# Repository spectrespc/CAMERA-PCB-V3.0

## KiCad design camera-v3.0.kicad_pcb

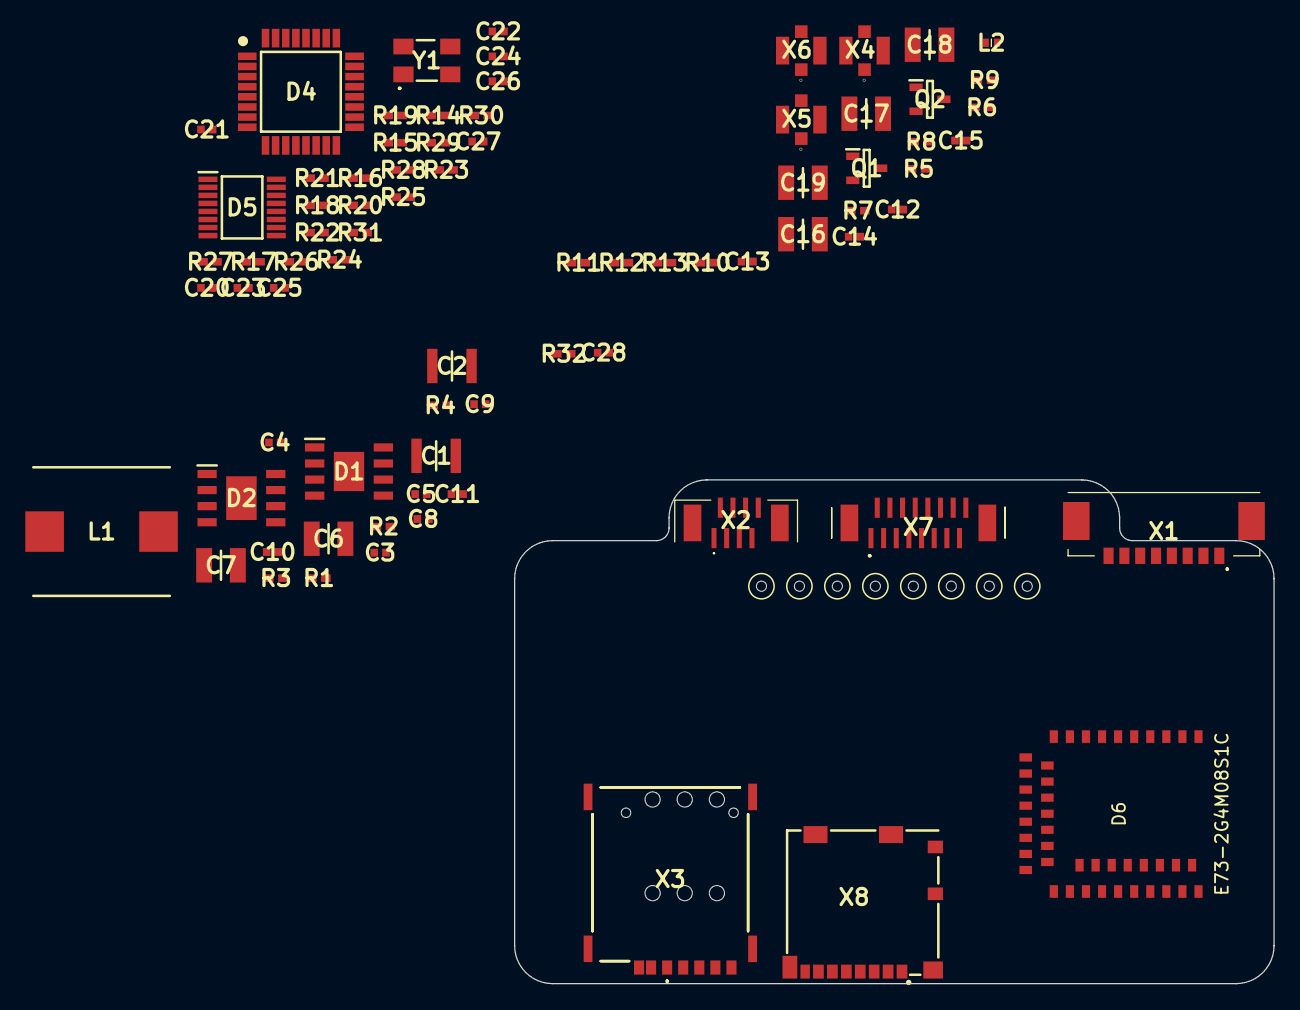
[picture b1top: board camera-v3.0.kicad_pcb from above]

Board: 2 copper layers, 60.0 x 39.8 mm, 79 parts (1 on the bottom side), 58 nets, no tracks yet.

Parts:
C1, C2: 10u; CAPC3225X150N
C3, C8: 150p; CAPC1005X55N
C4, C11: 15n; CAPC1005X55N
C5, C15: 0.1u; CAPC1005X55N
C6, C7, C16, C17, C18, C19: 22u; CAPC3225X270N
C9, C10, C20, C21, C22, C25, C26, C27, C28: 1u; CAPC1005X55N
C12, C13, C14, C23, C24: 16p; CAPC1005X55N
D1: TPS54334DDA; SOIC127P600X170-9N
D2: ADP1706ARDZ-3.3-R7; SOIC127P600X175-9N
D3: SIM7600E-H; IC_SIM7600E-H
D4: TUSB2046BVF; QFP80P900X900X160-32N
D5: GL823K; SOP64P600X175-16N
D6: E73-2G4M08S1C-52840
L1: IHLP4040DZER6R8M01; INDPM108102X400N
L2: 47n; LQW15CNR20J00B
Q1, Q2: BC849B; SOT95P230X110-3N
R1: 2k; RESC1005X40N
R2: 51.1; RESC1005X40N
R3: 30.1k; RESC1005X40N
R4, R13: 3k; RESC1005X40N
R5, R6, R7: 22; RESC1005X40N
R8, R9, R10, R11, R12: 4.7k; RESC1005X40N
R14, R18, R23, R32: 10k; RESC1005X40N
R15, R16, R17, R20, R21, R22: DNP; RESC1005X40N
R19: 1k5; RESC1005X40N
R24, R25, R26, R27, R28, R29, R30, R31: 15k; RESC1005X40N
X1: 53398-0867; 533980867
X2: 1734742-8; 17347428
X3: SIM8065-6-1-14-01-A; SIM8065611401A
X4, X5, X6: 73412-0110
X7: 1-1734742-6; 117347426
X8: 104031-0811; 1040310811
Y1: 6MHz; ECS4802030BDUTR

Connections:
+3V3: C10.1, C20.1, C21.1, C22.1, C25.1, C26.1, C28.1, D2.5, D2.6, D2.7, D4.3, D4.6, D4.25, D4.26, D5.9, D5.10, D5.13, D6.19, R12.2, R13.1, R14.1, R19.1, R23.2, R32.2, X2.3
+4V: C6.1, C7.1, C9.1, C16.1, C17.1, C18.1, C19.1, D2.1, D2.3, D2.4, D3.38, D3.39, D3.62, D3.63, L1.2, R2.1
ANT_AUX: D3.59, X6.1
ANT_GNSS: D3.79, L2.2, X5.1
ANT_MAIN: D3.82, X4.1
CAM_DM: D4.2, X7.13
CAM_DP: D4.1, R19.2, X7.14
DM1: D4.11, D5.16, R25.2
DM2: D3.12, D4.15, R27.2
DM3: D4.19, D6.29, R29.2
DM4: D4.23, R31.2
DP1: D4.12, D5.15, R24.2
DP2: D3.13, D4.16, R26.2
DP3: D4.20, D6.31, R28.2
DP4: D4.24, R30.2
GND: C1.2, C2.2, C3.2, C4.2, C6.2, C7.2, C9.2, C10.2, C11.1, C12.2, C13.2, C14.2, C15.1, C16.2, C17.2, C18.2, C19.2, C20.2, C21.2, C22.2, C23.2, C24.2, C25.2, C26.2, C27.2, C28.2, D1.4, D2.2, D2.9, D3.1, D3.2, D3.5, D3.10, D3.14, D3.37, D3.40, D3.41, D3.43, D3.57, D3.58, D3.60, D3.61, D3.64, D3.65, D3.77, D3.78, D3.80, D3.81, D4.7, D4.27, D4.28, D4.31, D5.1, D5.14, D6.5, D6.21, D6.24, Q1.2, Q2.2, R4.2, R10.2, R11.2, R18.1, R24.1, R25.1, R26.1, R27.1, R28.1, R29.1, R30.1, R31.1, X1.4, X1.5, X1.6, X1.MP1, X1.MP2, X2.5, X2.6, X2.MP1, X2.MP2, X3.C5, X3.G1, X3.G2, X3.G3, X3.G4, X4.2, X4.3, X4.4, X5.2, X5.3, X5.4, X6.2, X6.3, X6.4, X7.8, X7.11, X7.MP1, X7.MP2, X8.6, X8.9, X8.10, X8.11, X8.13, X8.14, Y1.2, Y1.4
unnamed: C3.1, D1.6, R1.1
unnamed: C4.1, R1.2
unnamed: C5.1, D1.1
unnamed: C5.2, D1.3, L1.1
unnamed: C8.1, R2.2, R3.1
unnamed: C8.2, D1.5, R3.2, R4.1
unnamed: C11.2, D2.8
unnamed: C23.1, D4.30, Y1.1
unnamed: C24.1, D4.29, Y1.3
unnamed: D3.3, Q1.3
unnamed: D3.4, Q2.3
unnamed: D3.11, R12.1
unnamed: D4.4, R14.2
unnamed: D4.8, R18.2
unnamed: D4.10, D4.14, D4.18, D4.22, R23.1
unnamed: D6.26, R32.1
unnamed: L2.1, R13.2
unnamed: Q1.1, R8.2, R10.1
unnamed: Q2.1, R9.2, R11.1
unnamed: R5.2, X3.C2
unnamed: R6.2, X3.C3
unnamed: R7.2, X3.C7
unnamed: R15.2, X7.1
unnamed: R16.2, X7.3
unnamed: R17.2, X7.5
unnamed: R20.1, X7.2
unnamed: R21.1, X7.4
unnamed: R22.1, X7.6
SD_CD: D5.11, X8.12
SD_CLK: D5.4, R15.1, X8.5
SD_CMD: D5.5, R20.2, X8.3
SD_D0: D5.3, R16.1, X8.7
SD_D1: D5.2, R21.2, X8.8
SD_D2: D5.7, R17.1, X8.1
SD_D3: D5.6, R22.2, X8.2
SD_POW: C27.1, D5.8, X8.4
SIM_CLK: C13.1, D3.19, R6.1
SIM_DET: D3.53, X3.CD1
SIM_IO: C12.1, D3.17, R7.1
SIM_RST: C14.1, D3.18, R5.1
SIM_VCC: C15.2, D3.20, X3.C1
Vin: C1.1, C2.1, D1.2, X1.1, X1.2, X1.3, X2.8

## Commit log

2021-04-15 fix
    fix lib
2021-05-12 Разработано расположение компонентов
2021-05-14 Добавил ещё компонентов
2021-05-14 Мелкие фиксы
2021-05-25 Заменены слоты SD и SIM на более дешевые
2021-05-25 Даташит по sim7600
2021-07-02 добавил даташит по беспроводному модулю
2021-07-02 Добавил разъемы
2021-07-06 06.07.2021
